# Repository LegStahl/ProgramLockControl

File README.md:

# ProgramLockControl
## Description
This device is supposed to use for controlling the door. It can open the door if the right IButton is pressed, also it has a button to open the door.
Device controls magnetic lock. Internally device can coolect info about opening the door, for example: key number, time of enter and etc.
Also device can another control high current till 5A load. This connection is supposed to be used for LED strip.
## Microcontroller and power schema V1.0
In the image below schema of the mcu and power.
<div style="text-align: center;">
    
</div>

## Peripheria V1.0
In the image below schema of peripherias of MCU.
<div style="text-align: center;">
    
</div>

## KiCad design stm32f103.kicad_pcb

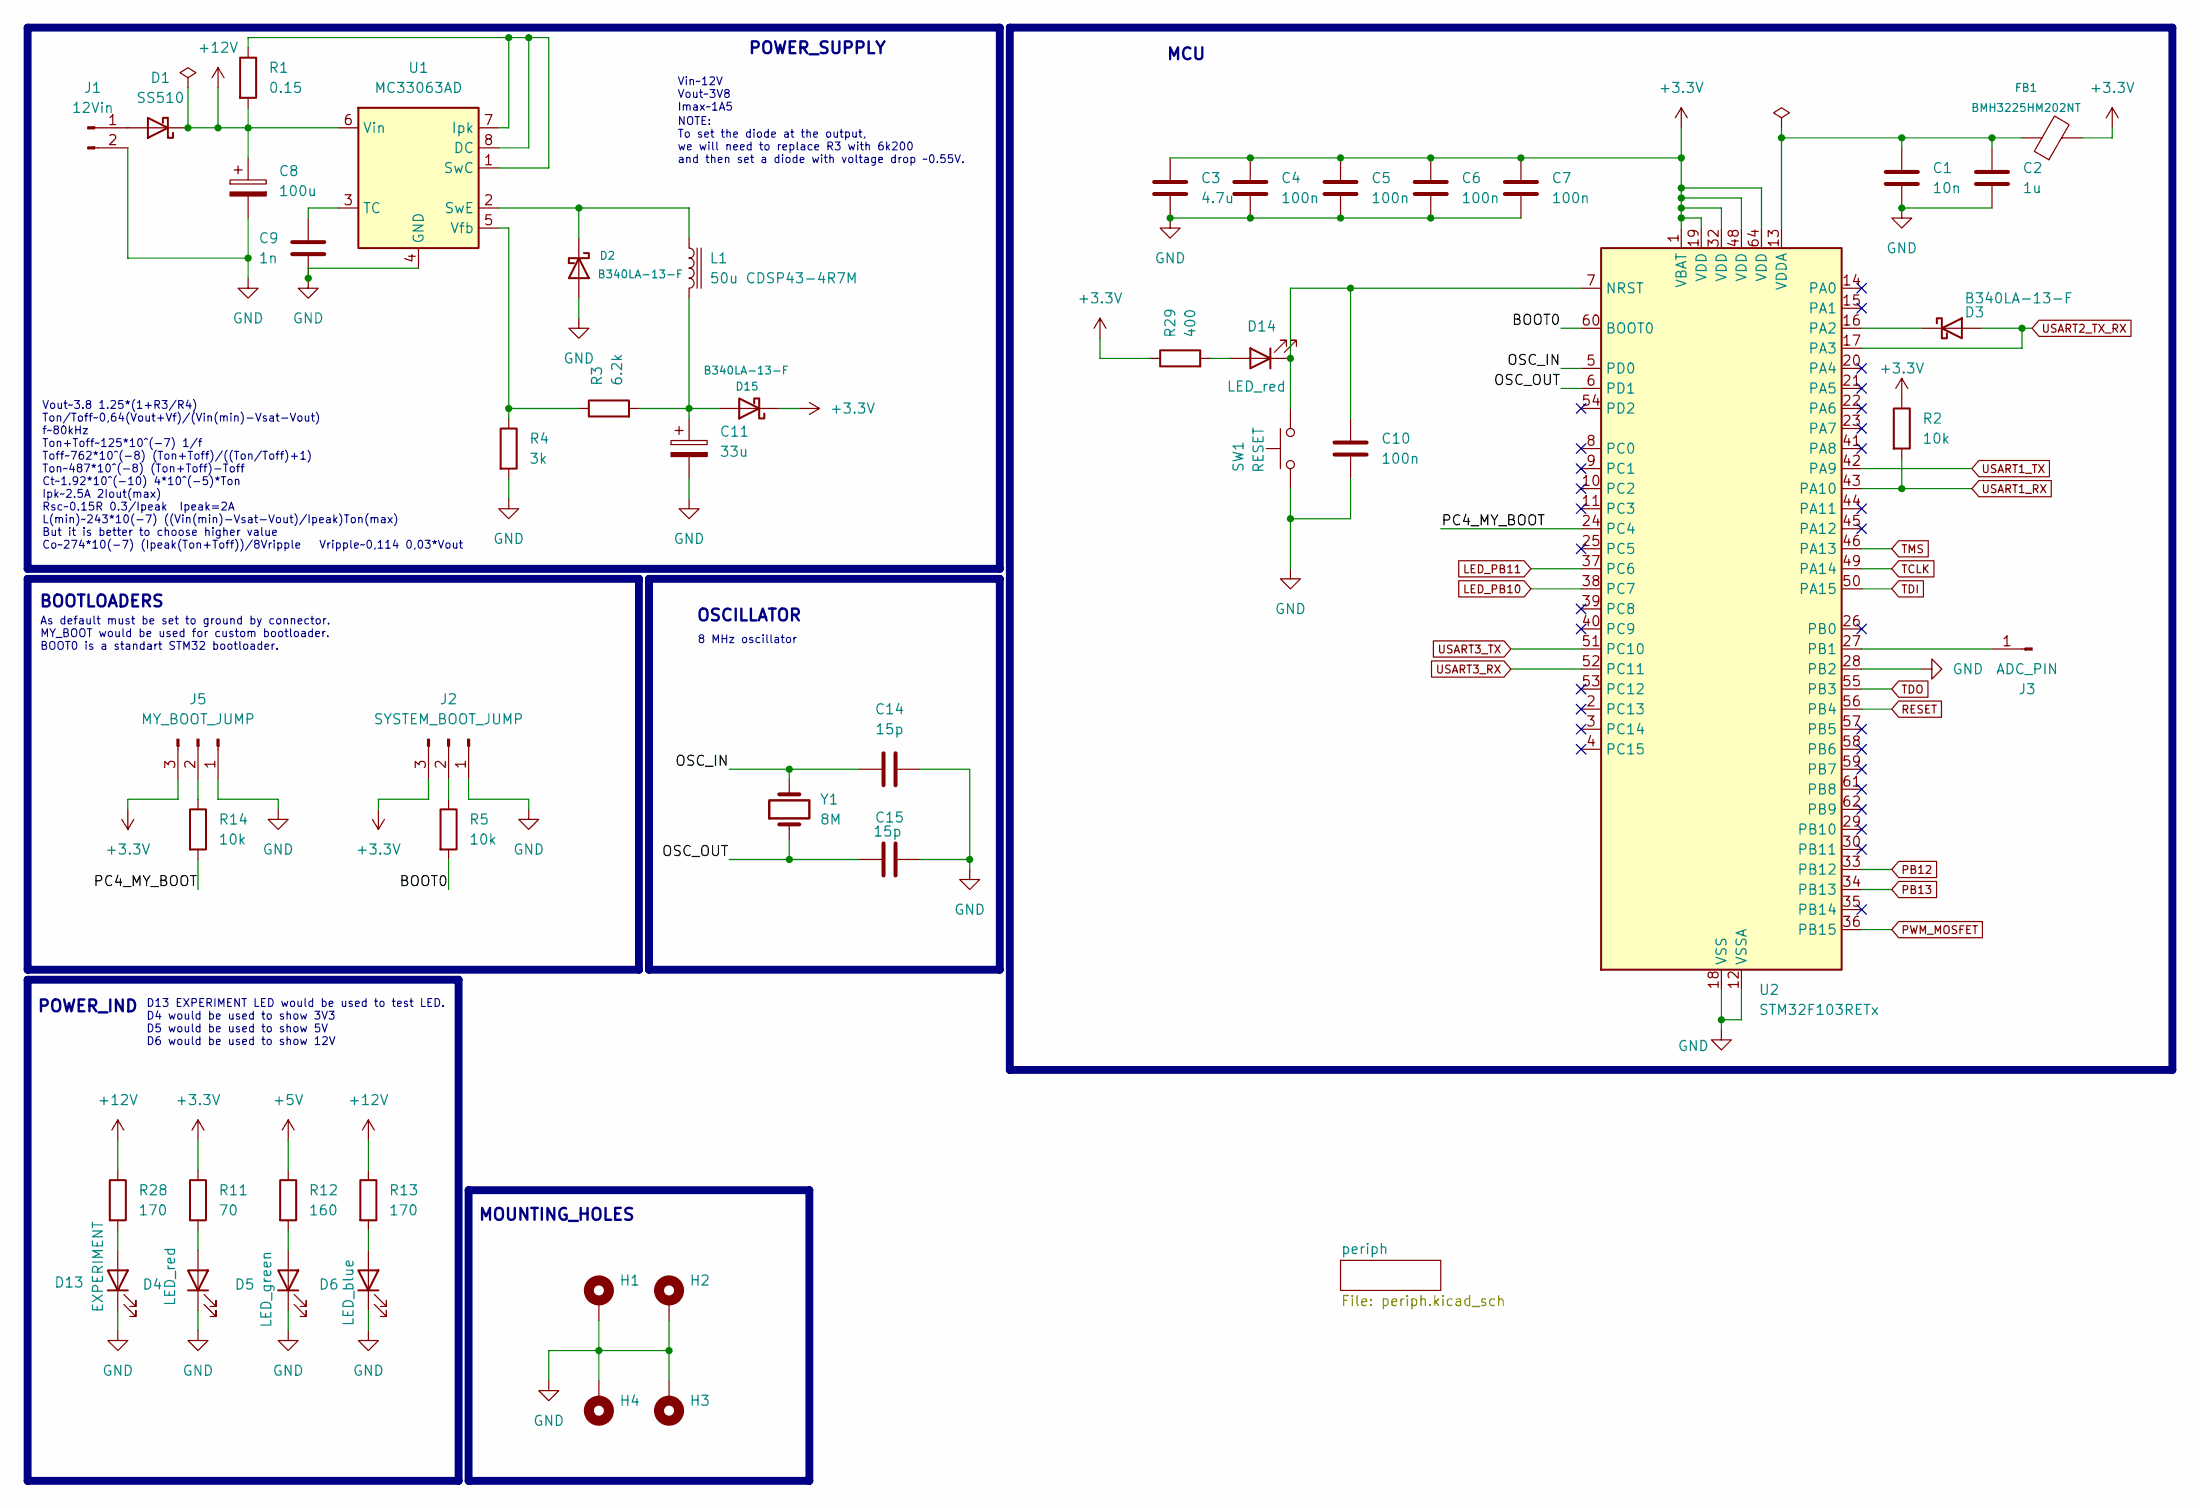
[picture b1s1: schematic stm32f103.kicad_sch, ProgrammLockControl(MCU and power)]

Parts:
C1: 10n; C_1206_3216Metric_Pad1.33x1.80mm_HandSolder
C2: 1u; C_1206_3216Metric_Pad1.33x1.80mm_HandSolder
C3: 4.7u; C_1206_3216Metric_Pad1.33x1.80mm_HandSolder
C4, C5, C6, C7, C10: 100n; C_1206_3216Metric_Pad1.33x1.80mm_HandSolder
C8: 100u; CP_Elec_6.3x5.4
C9: 1n; C_1812_4532Metric_Pad1.57x3.40mm_HandSolder
C11: 33u; CP_Elec_6.3x5.4
C14, C15: 15p; C_1206_3216Metric_Pad1.33x1.80mm_HandSolder
D1: SS510; D_SMA_Handsoldering
D2, D3, D15: B340LA-13-F; D_SMA_Handsoldering
D4, D14: LED_red; LED_1206_3216Metric_Pad1.42x1.75mm_HandSolder
D5: LED_green; LED_1206_3216Metric_Pad1.42x1.75mm_HandSolder
D6: LED_blue; LED_1206_3216Metric_Pad1.42x1.75mm_HandSolder
D13: EXPERIMENT; LED_Everlight-SMD3528_3.5x2.8mm_67-21ST
FB1: BMH3225HM202NT; L_1210_3225Metric_Pad1.42x2.65mm_HandSolder
H1, H2, H3, H4: MountingHole_Pad; MountingHole_3.2mm_M3_Pad_Via
J1: 12Vin; PhoenixContact_MC_1,5_2-G-3.5_1x02_P3.50mm_Horizontal
J2: SYSTEM_BOOT_JUMP; PinHeader_1x03_P2.54mm_Vertical
J3: ADC_PIN; PinHeader_1x01_P2.54mm_Vertical
J5: MY_BOOT_JUMP; PinHeader_1x03_P2.54mm_Vertical
L1: 50u CDSP43-4R7M; L_TracoPower_TCK-047_5.2x5.8mm
R1: 0.15; R_2010_5025Metric_Pad1.40x2.65mm_HandSolder
R2, R5, R14: 10k; R_1206_3216Metric_Pad1.30x1.75mm_HandSolder
R3: 6.2k; R_1206_3216Metric_Pad1.30x1.75mm_HandSolder
R4: 3k; R_1206_3216Metric_Pad1.30x1.75mm_HandSolder
R11: 70; R_1206_3216Metric_Pad1.30x1.75mm_HandSolder
R12: 160; R_1206_3216Metric_Pad1.30x1.75mm_HandSolder
R13, R28: 170; R_1206_3216Metric_Pad1.30x1.75mm_HandSolder
R29: 400; R_1206_3216Metric_Pad1.30x1.75mm_HandSolder
SW1: RESET; SW_SPST_Omron_B3FS-100xP
U1: MC33063AD; SO-8_3.9x4.9mm_P1.27mm
U2: STM32F103RETx; LQFP-64_10x10mm_P0.5mm
Y1: 8M; Crystal_HC49-4H_Vertical

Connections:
+3.3V: C3.1, C4.1, C5.1, C6.1, C7.1, D15.1 (K), FB1.2, J2.3, J5.3, R2.1, R11.1, R29.1, U2.1 (VBAT), U2.19 (VDD), U2.32 (VDD), U2.48 (VDD), U2.64 (VDD); also elsewhere on the board
+5V: R12.1; also elsewhere on the board
+12V: C8.1, D1.1 (K), R1.2, R13.1, R28.1, U1.6 (Vin); also elsewhere on the board
/BOOT0: R5.2, U2.60 (BOOT0)
/OSC_IN: C14.1, U2.5 (PD0), Y1.2
/OSC_OUT: C15.1, U2.6 (PD1), Y1.1
/PC4_MY_BOOT: R14.2, U2.24 (PC4)
GND: C1.2, C2.2, C3.2, C4.2, C5.2, C6.2, C7.2, C8.2, C9.2, C10.2, C11.2, C14.2, C15.2, D2.2 (A), D4.1 (K), D5.1 (K), D6.1 (K), D13.1 (K), H1.1, H2.1, H3.1, H4.1, J1.2, J2.1, J5.1, R4.2, SW1.1, U1.4 (GND), U2.12 (VSSA), U2.18 (VSS), U2.28 (PB2), U2.31 (VSS), U2.47 (VSS), U2.63 (VSS); also elsewhere on the board
LED_PB10: U2.38 (PC7); also elsewhere on the board
LED_PB11: U2.37 (PC6); also elsewhere on the board
unnamed: D1.2 (A), J1.1
unnamed: D2.1 (K), L1.1, U1.2 (SwE)
unnamed: D3.1 (K), U2.16 (PA2)
unnamed: D4.2 (A), R11.2
unnamed: D5.2 (A), R12.2
unnamed: D6.2 (A), R13.2
unnamed: D13.2 (A), R28.2
unnamed: D14.2 (A), R29.2
unnamed: C10.1, D14.1 (K), SW1.2, U2.7 (NRST)
unnamed: C11.1, D15.2 (A), L1.2, R3.2
unnamed: J2.2, R5.1
unnamed: J3.1, U2.27 (PB1)
unnamed: J5.2, R14.1
unnamed: R1.1, U1.1 (SwC), U1.7 (Ipk), U1.8 (DC)
unnamed: C9.1, U1.3 (TC)
unnamed: R3.1, R4.1, U1.5 (Vfb)
unnamed: C1.1, C2.1, FB1.1, U2.13 (VDDA)
PB12: U2.33 (PB12); also elsewhere on the board
PB13: U2.34 (PB13); also elsewhere on the board
PWM_MOSFET: U2.36 (PB15); also elsewhere on the board
RESET: U2.56 (PB4); also elsewhere on the board
TCLK: U2.49 (PA14); also elsewhere on the board
TDI: U2.50 (PA15); also elsewhere on the board
TDO: U2.55 (PB3); also elsewhere on the board
TMS: U2.46 (PA13); also elsewhere on the board
USART1_RX: R2.2, U2.43 (PA10); also elsewhere on the board
USART1_TX: U2.42 (PA9); also elsewhere on the board
USART2_TX_RX: D3.2 (A), U2.17 (PA3); also elsewhere on the board
USART3_RX: U2.52 (PC11); also elsewhere on the board
USART3_TX: U2.51 (PC10); also elsewhere on the board

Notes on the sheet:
Vin~12V Vout~3V8 Imax~1A5
MOUNTING_HOLES
D13 EXPERIMENT LED would be used to test LED. D4 would be used to show 3V3 D5 would be used to show 5V D6 would be used to show 12V
POWER_IND
MCU
NOTE: To set the diode at the output, we will need to replace R3 with 6k200 and then set a diode with voltage drop ~0.55V.
Vout~3.8 1.25*(1+R3/R4) Ton/Toff~0,64(Vout+Vf)/(Vin(min)-Vsat-Vout) f~80kHz Ton+Toff~125*10^(-7) 1/f Toff~762*10^(-8) (Ton+Toff)/((Ton/Toff)+1) Ton~487*10^(-8) (Ton+Toff)-Toff Ct~1.92*10^(-10) 4*10^(-5)*Ton Ipk~2.5A 2Iout(max) Rsc~0.15R 0.3/Ipeak Ipeak=2A L(min)~243*10(-7) ((Vin(min)-Vsat-Vout)/Ipe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
OSCILLATOR
BOOTLOADERS
As default must be set to ground by connector. MY_BOOT would be used for custom bootloader. BOOT0 is a standart STM32 bootloader.
POWER_SUPPLY
8 MHz oscillator

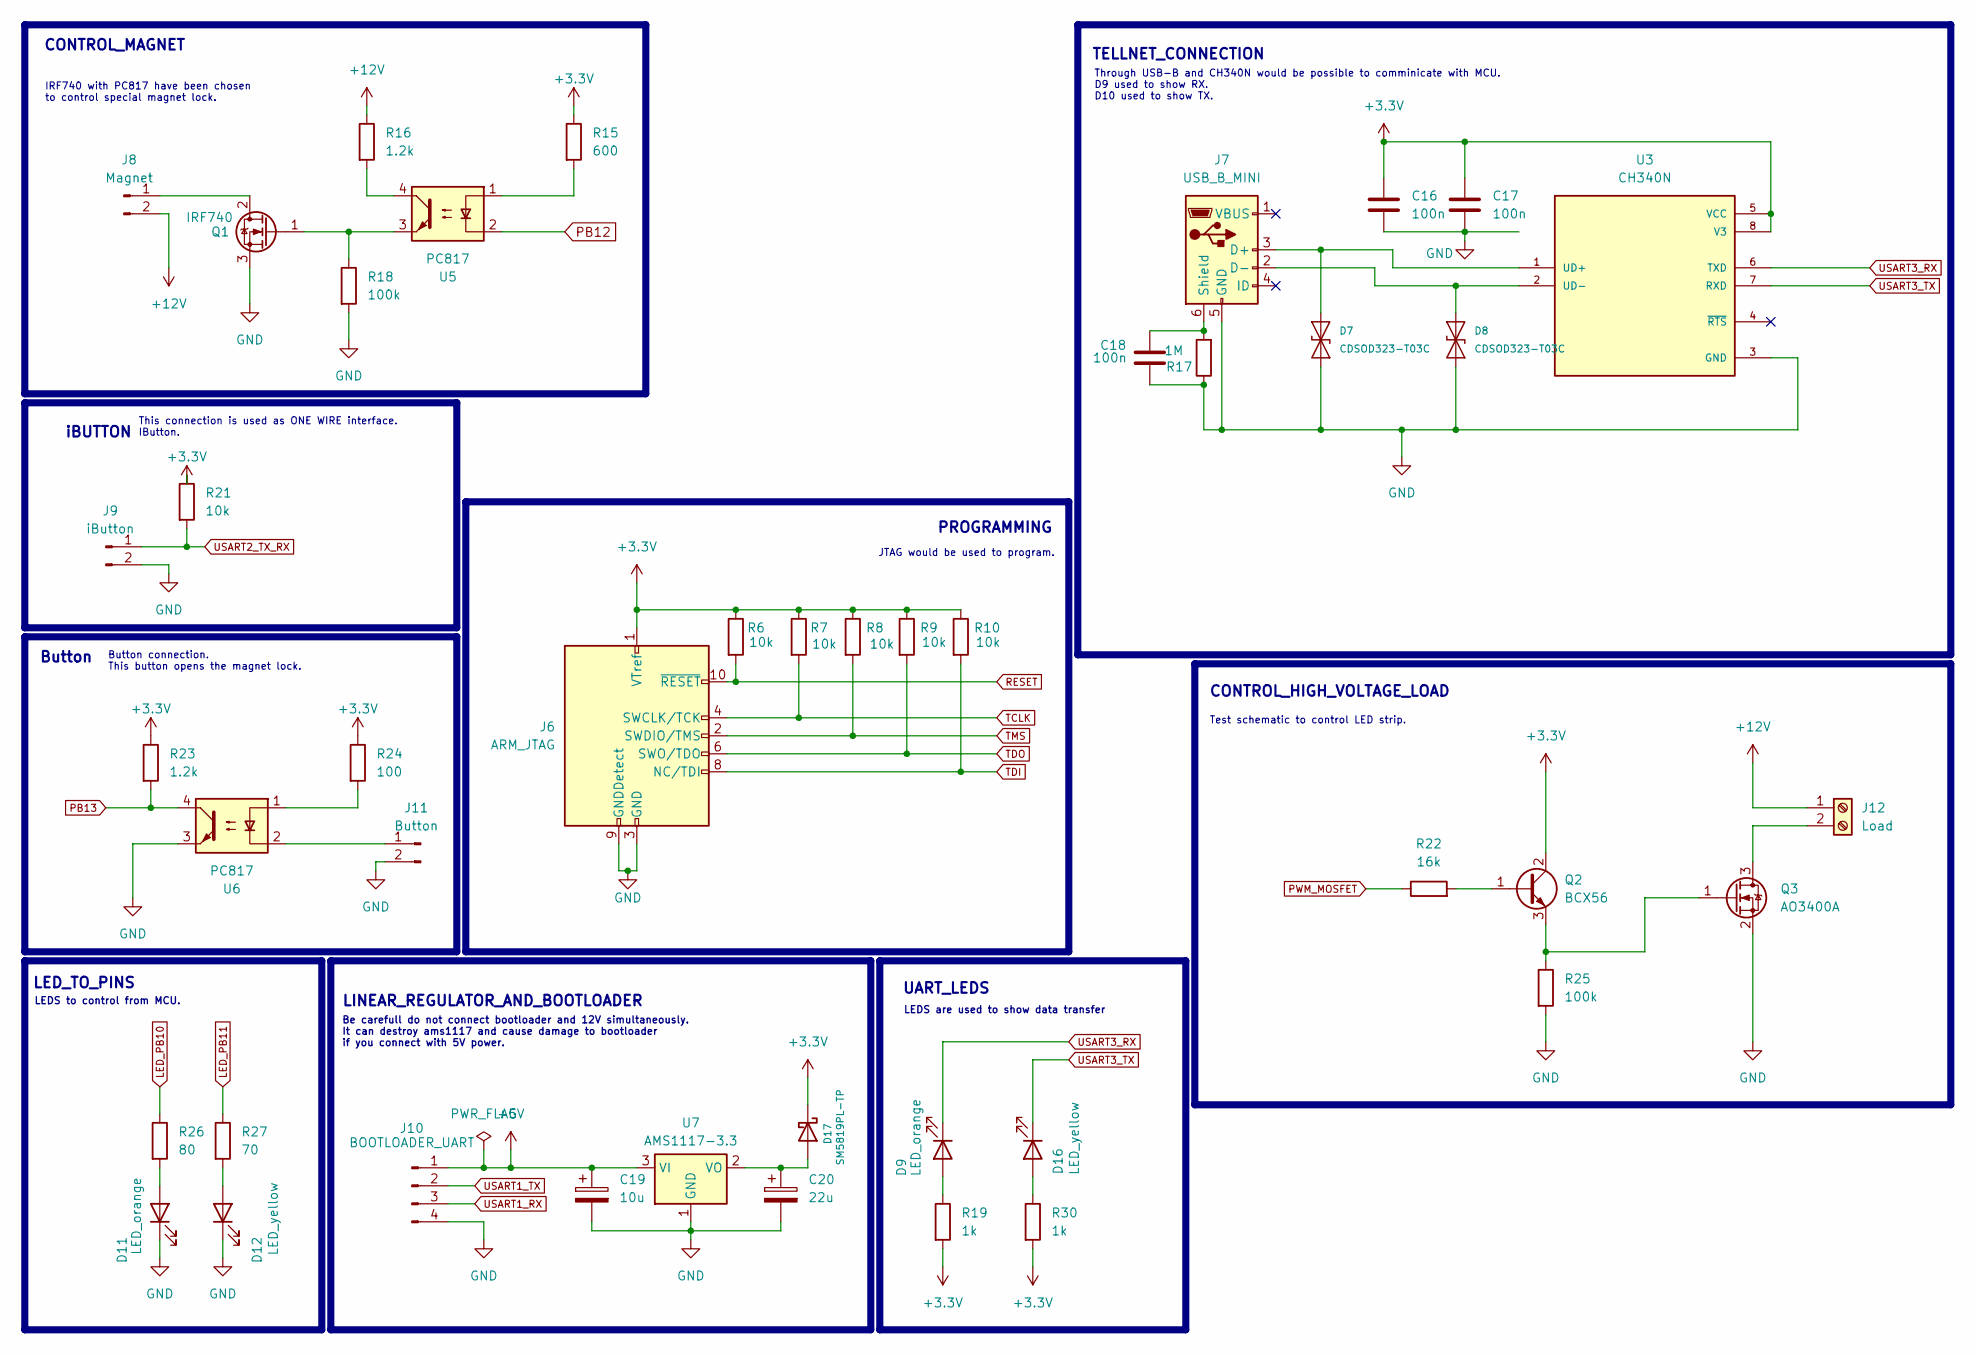
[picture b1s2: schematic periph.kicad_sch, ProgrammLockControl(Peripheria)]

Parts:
C16, C17, C18: 100n; C_1206_3216Metric_Pad1.33x1.80mm_HandSolder
C19: 10u; CP_EIA-3216-12_Kemet-S_HandSolder
C20: 22u; CP_EIA-3216-12_Kemet-S_HandSolder
D7, D8: CDSOD323-T03C; D_SOD-323_HandSoldering
D9, D11: LED_orange; LED_1206_3216Metric
D12, D16: LED_yellow; LED_1206_3216Metric
D17: SM5819PL-TP; D_SOD-123F
J6: ARM_JTAG; PinHeader_2x05_P2.54mm_Vertical
J7: USB_B_MINI; USB_Mini-B_Lumberg_2486_01_Horizontal
J8: Magnet; PhoenixContact_MC_1,5_2-G-3.5_1x02_P3.50mm_Horizontal
J9: iButton; PhoenixContact_MC_1,5_2-G-3.5_1x02_P3.50mm_Horizontal
J10: BOOTLOADER_UART; PinHeader_1x04_P2.54mm_Vertical
J11: Button; PhoenixContact_MC_1,5_2-G-3.5_1x02_P3.50mm_Horizontal
J12: Load; TerminalBlock_Phoenix_MKDS-1,5-2-5.08_1x02_P5.08mm_Horizont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
Q1: IRF740; TO-220-3_Vertical
Q2: BCX56; SOT-89-3_Handsoldering
Q3: AO3400A; SOT-23_Handsoldering
R6, R7, R8, R9, R10, R21: 10k; R_1206_3216Metric_Pad1.30x1.75mm_HandSolder
R15: 600; R_1206_3216Metric_Pad1.30x1.75mm_HandSolder
R16, R23: 1.2k; R_1206_3216Metric_Pad1.30x1.75mm_HandSolder
R17: 1M; R_1206_3216Metric_Pad1.30x1.75mm_HandSolder
R18, R25: 100k; R_1206_3216Metric_Pad1.30x1.75mm_HandSolder
R19, R30: 1k; R_1206_3216Metric_Pad1.30x1.75mm_HandSolder
R22: 16k; R_1206_3216Metric_Pad1.30x1.75mm_HandSolder
R24: 100; R_1206_3216Metric_Pad1.30x1.75mm_HandSolder
R26: 80; R_1206_3216Metric_Pad1.30x1.75mm_HandSolder
R27: 70; R_1206_3216Metric_Pad1.30x1.75mm_HandSolder
U3: CH340N; SOIC127P600X160-8N; PARTREV V3C
U5, U6: PC817; SMDIP-4_W7.62mm
U7: AMS1117-3.3; SOT-223-3_TabPin2

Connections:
+3.3V: C16.1, C17.1, D17.1 (K), J6.1 (VTref), Q2.2 (C), R6.1, R7.1, R8.1, R9.1, R10.1, R15.1, R19.2, R21.1, R23.1, R24.1, R30.2, U3.5 (VCC), U3.8 (V3); also elsewhere on the board
+5V: C19.1, J10.1, U7.3 (VI); also elsewhere on the board
+12V: J8.2, J12.1, R16.1; also elsewhere on the board
GND: C16.2, C17.2, C18.2, C19.2, C20.2, D7.1 (A1), D8.1 (A1), D11.1 (K), D12.1 (K), J6.3 (GND), J6.5 (GND), J6.9 (GNDDetect), J7.5 (GND), J9.2, J10.4, J11.2, Q1.3 (S), Q3.2 (S), R17.1, R18.2, R25.2, U3.3 (GND), U6.3, U7.1 (GND); also elsewhere on the board
LED_PB10: R26.1; also elsewhere on the board
LED_PB11: R27.1; also elsewhere on the board
unnamed: D7.2 (A2), J7.3 (D+), U3.1 (UD+)
unnamed: D8.2 (A2), J7.2 (D-), U3.2 (UD-)
unnamed: D9.2 (A), R19.1
unnamed: D11.2 (A), R26.2
unnamed: D12.2 (A), R27.2
unnamed: D16.2 (A), R30.1
unnamed: C20.1, D17.2 (A), U7.2 (VO)
unnamed: C18.1, J7.6 (Shield), R17.2
unnamed: J8.1, Q1.2 (D)
unnamed: J11.1, U6.2
unnamed: J12.2, Q3.3 (D)
unnamed: Q1.1 (G), R18.1, U5.3
unnamed: Q2.1 (B), R22.2
unnamed: Q2.3 (E), Q3.1 (G), R25.1
unnamed: R15.2, U5.1
unnamed: R16.2, U5.4
unnamed: R24.2, U6.1
PB12: U5.2; also elsewhere on the board
PB13: R23.2, U6.4; also elsewhere on the board
PWM_MOSFET: R22.1; also elsewhere on the board
RESET: J6.10 (~RESET), R6.2; also elsewhere on the board
TCLK: J6.4 (SWCLK/TCK), R7.2; also elsewhere on the board
TDI: J6.8 (NC/TDI), R10.2; also elsewhere on the board
TDO: J6.6 (SWO/TDO), R9.2; also elsewhere on the board
TMS: J6.2 (SWDIO/TMS), R8.2; also elsewhere on the board
USART1_RX: J10.3; also elsewhere on the board
USART1_TX: J10.2; also elsewhere on the board
USART2_TX_RX: J9.1, R21.2; also elsewhere on the board
USART3_RX: D9.1 (K), U3.6 (TXD); also elsewhere on the board
USART3_TX: D16.1 (K), U3.7 (RXD); also elsewhere on the board

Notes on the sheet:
Be carefull do not connect bootloader and 12V simultaneously. It can destroy ams1117 and cause damage to bootloader if you connect with 5V power.
CONTROL_MAGNET
LEDS to control from MCU.
Test schematic to control LED strip.
JTAG would be used to program.
Button
LED_TO_PINS
TELLNET_CONNECTION
IRF740 with PC817 have been chosen to control special magnet lock.
Button connection. This button opens the magnet lock.
Through USB-B and CH340N would be possible to comminicate with MCU. D9 used to show RX. D10 used to show TX.
UART_LEDS
LINEAR_REGULATOR_AND_BOOTLOADER
LEDS are used to show data transfer
PROGRAMMING
iBUTTON
This connection is used as ONE WIRE interface. IButton.
CONTROL_HIGH_VOLTAGE_LOAD

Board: 4 copper layers, 91 parts (0 on the bottom side), 57 nets, no tracks yet.

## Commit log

2025-11-13 First PCB project was done before git commits version:1.0
2025-11-14 Some rearrangements have been made in schematics
2025-11-14 Frames in schematics has been added. Types of mounting holes has been replaced
2025-11-14 Images of first_version added
2025-11-14 Comments have been added to the schemas
2025-11-19 Images of schema has been added and some components value has been changed@
2025-11-20 Footprints of bootloaders and boots have been changed also has been cahnged ADC pin header, reset LED have been added, and diode for switch
2025-11-25 Calculations have been made for MC33063 with diode at the output
2025-11-25 CH340N has been added. Previous version was wrong. Pin V3 was wrong placed and was connected to GND
2025-11-25 File deleted
2025-11-28 Stack has been chosen: 4 layer SIG+GND+PWR+SIG. Componetns have been divided in groups pcb
2025-11-28 Shottky diod has been added to provide protection for AMS1117-3.3
